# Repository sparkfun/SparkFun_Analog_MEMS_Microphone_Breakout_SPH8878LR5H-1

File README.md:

SparkFun Analog MEMS Microphone Breakout - SPH8878LR5H-1
========================================

[*SparkFun MEMS Microphone Breakout (ICS-40180) [BOB-18011]*](https://www.sparkfun.com/products/19389)

The SparkFun Analog MEMS Microphone Breakout makes it easy to work with the SPH8878LR5H-1 analog microphone from Knowles. This board features an OpAmp to bring output of the microphone to a usable level, allowing you to plug directly into an ADC on a microcontroller or something like the [SparkFun Spectrum Shield](https://www.sparkfun.com/products/13116).

In addition to amplifying the signal, the OpAmp adds a bias voltage of 1/2 VCC. With sound sources such as a normal speaking voice a few feet away from the microphone, the AUD output signal will be at about 200mV peak-to-peak. Also note, this low profile microphone has its port on the bottom side, so the microphone can be mounted flush to the outer surface of your enclosure. This microphone is omni-directional, which means it does a good job of picking up sound sources from all directions.

Repository Contents
-------------------

* **/Documentation** - Data sheets, additional product information
* **/Hardware** - Eagle design files (.brd, .sch)
* **/Hardware/Production** - Production panel files (.brd)

Documentation
--------------
* **[Hookup Guide](https://learn.sparkfun.com/tutorials/analog-mems-microphone-breakout---sph8878lr5h-1-hookup-guide)** - Basic hookup guide for the SparkFun MEMS microphone breakout.

Product Versions
---------------
* **[BOB-09868](https://www.sparkfun.com/products/retired/9868)** - SparkFun MEMS Microphone Breakout - INMP401 (ADMP401)
* **[BOB-18011](https://www.sparkfun.com/products/18011)** - SparkFun Analog MEMS Microphone Breakout - ICS-40180 
* **[BOB-19389](https://www.sparkfun.com/products/19389)** -  SparkFun Analog MEMS Microphone Breakout - SPH8878LR5H-1

License Information
-------------------

This product is _**open source**_! 

Please review the LICENSE.md file for license information. 

If you have any questions or concerns on licensing, please contact technical support on our [SparkFun forums](https://forum.sparkfun.com/viewforum.php?f=152).

Distributed as-is; no warranty is given.

- Your friends at SparkFun.

_<COLLABORATION CREDIT>_

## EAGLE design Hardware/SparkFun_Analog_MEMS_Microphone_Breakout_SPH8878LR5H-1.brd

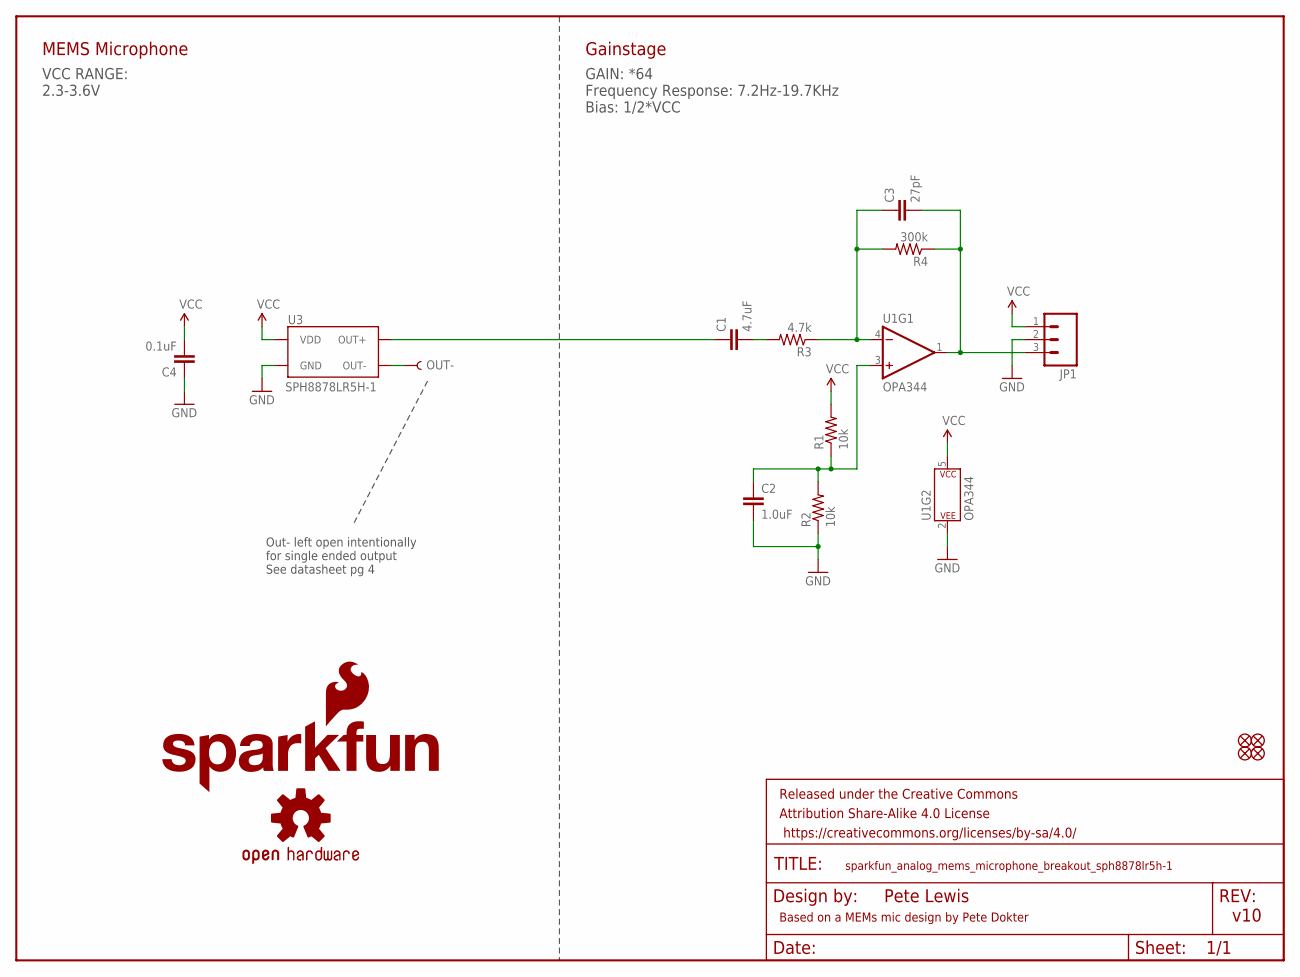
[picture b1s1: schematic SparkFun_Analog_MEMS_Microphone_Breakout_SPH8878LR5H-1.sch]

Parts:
C1: 4.7uF; 0603
C2: 1.0uF; 0603
C3: 27pF; 0603
C4: 0.1uF; 0603
FD1, FD2, FD3, FD4: FIDUCIALUFIDUCIAL; FIDUCIAL-MICRO
FRAME2: FRAME-LETTER; CREATIVE_COMMONS
JP1: CONN_031X03_NO_SILK; 1X03_NO_SILK
LOGO1: SFE_LOGO_FLAME.1_INCH; SFE_LOGO_FLAME_.1
LOGO2: OSHW-LOGOMINI; OSHW-LOGO-MINI
OUT-: TEST-POINTTP_15TH_THRU; TP_15TH
R1, R2: 10k; 0603
R3: 4.7k; 0603
R4: 300k; 0603
U1: OPA344; SOT23-5
U3: SPH8878LR5H-1

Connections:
AUD: C3.2, JP1.3, R4.1, U1.1 (OUT)
GND: C2.2, C4.1, JP1.2, R2.1, U1.2 (P$V-), U3.2 (GND), U3.3 (GND), U3.4 (GND)
unnamed: C1.1, U3.1 (OUT+)
unnamed: C3.1, R3.1, R4.2, U1.4 (-IN)
unnamed: OUT-.1, U3.6 (OUT-)
unnamed: C1.2, R3.2
unnamed: C2.1, R1.1, R2.2, U1.3 (+IN)
VCC: C4.2, JP1.1, R1.2, U1.5 (P$V+), U3.5 (VDD)

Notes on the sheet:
v10
Pete Lewis
VCC RANGE: 2.3-3.6V
MEMS Microphone
Gainstage
GAIN: *64 Frequency Response: 7.2Hz-19.7KHz Bias: 1/2*VCC
Out- left open intentionally for single ended output See datasheet pg 4
Based on a MEMs mic design by Pete Dokter

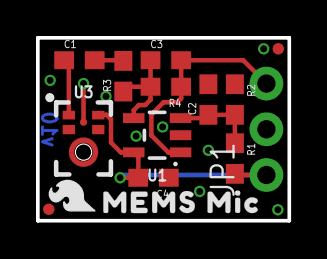
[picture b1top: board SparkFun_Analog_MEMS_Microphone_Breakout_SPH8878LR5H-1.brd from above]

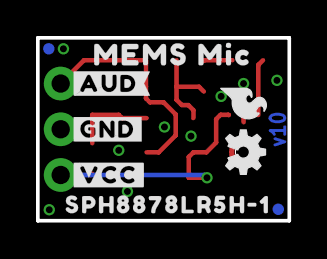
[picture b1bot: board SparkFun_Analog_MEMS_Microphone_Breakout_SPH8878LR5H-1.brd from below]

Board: 2 copper layers, 14.0 x 10.2 mm, 26 parts (10 on the bottom side), 8 nets.

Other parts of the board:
LOGO3: SFE_LOGO_FLAME.1_INCH; SFE_LOGO_FLAME_.1
U$2, U$7: MEMS_MIC0
U$3: #GND#0
U$4: #VCC#0
U$5: #AUD#0
U$9: SPH8878LR5H#10

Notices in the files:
parts and their libraries:
SparkFun-Resistors: Licensing: Creative Commons ShareAlike 4.0 International - https://creativecommons.org/licenses/by-sa/4.0
SparkFun-Aesthetics: Released under the Creative Commons Attribution Share-Alike 4.0 License
SparkFun-Aesthetics: https://creativecommons.org/licenses/by-sa/4.0
